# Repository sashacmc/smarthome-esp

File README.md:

# smarthome-esp
Eagle schemes for my esp8266 boards

## esp07_1w.*
Simple board to route 1-wire devices by esp07.
Fitted to standard phone socket.

## esp07_4PIO_6S_v2.*
My main smarthome esp07 board.
Provide:
* Four 220V outputs.
* Six dry contact (5V) inputs
* Two ext power (12V)
* Measure temperature and humidity by AM2302
* Measure illuminate by TSL2561

## esp07_co2.*
My first esp07 board
Provide:
* Measure temperature and pressure by BMP280
* Measuring CO2 level by MH-Z14

HAS BUGS WITH POWER CONSUMPTION FOR MH-Z14!!!

## esp07_ups.*
Board to control UPS by emulating power button pressing.
Has two power sources (from line and from UPS)

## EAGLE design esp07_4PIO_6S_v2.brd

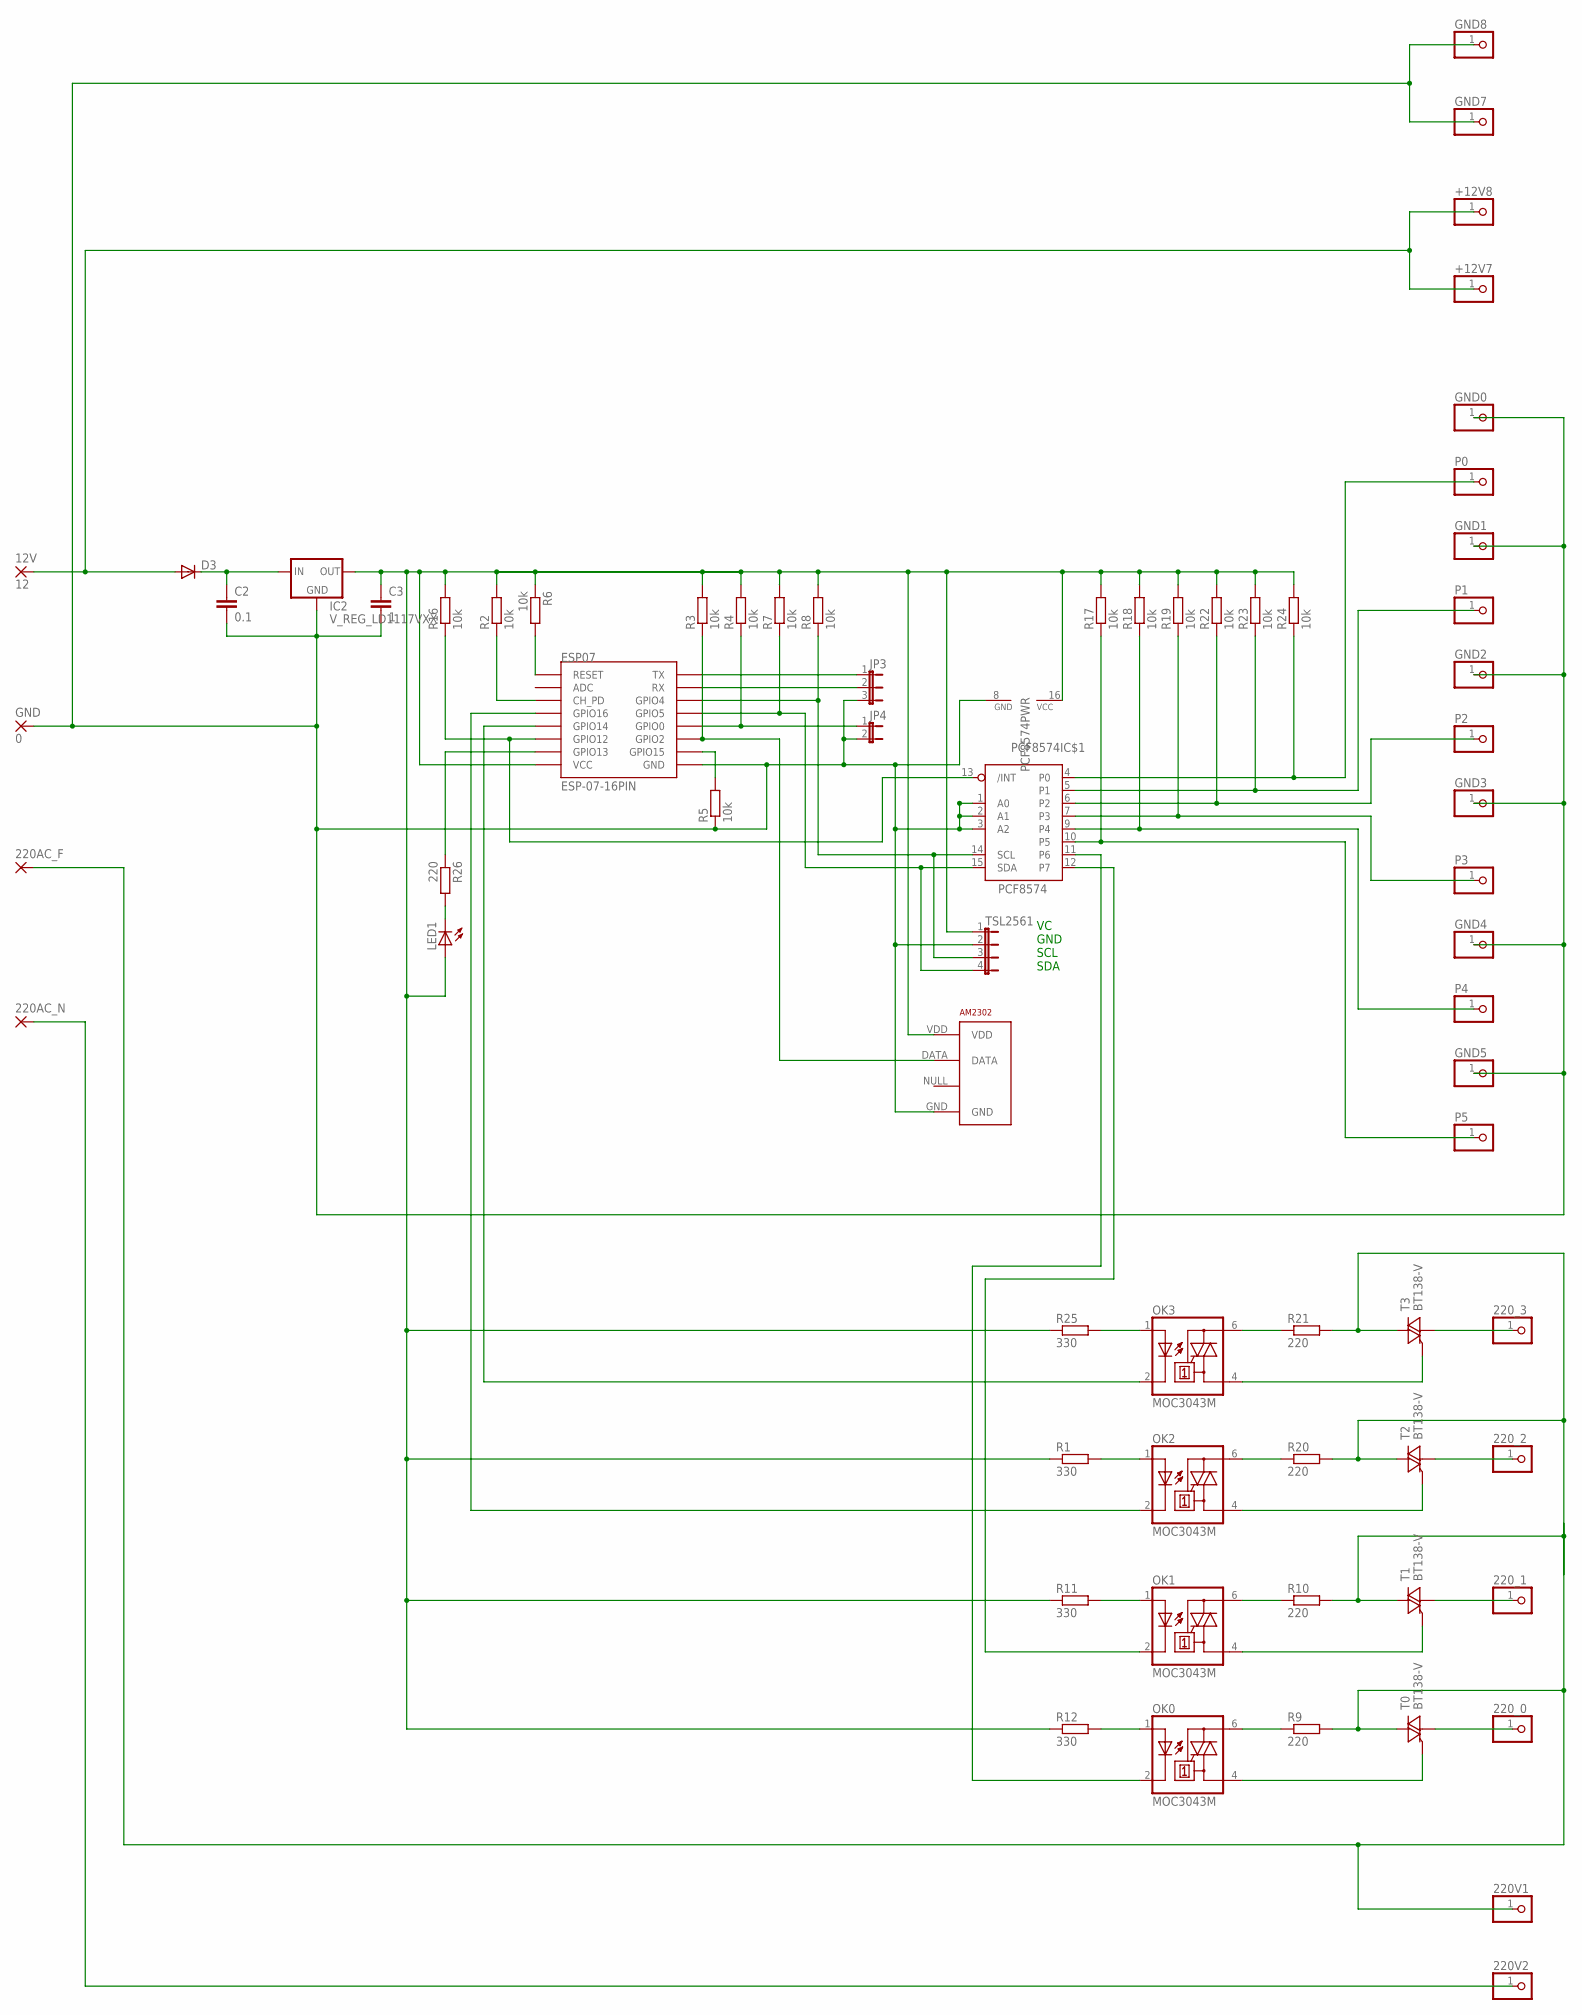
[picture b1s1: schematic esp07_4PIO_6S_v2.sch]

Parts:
12V: 12; 2,54/0,9
220AC_F, 220AC_N: 1,6/0,9
220V1, 220V2, 220_0, 220_1, 220_2, 220_3: PINHD-1X1; 1X01
+12V7, +12V8: PINHD-1X1; 1X01
AM2302: RHT03_DHT-22_AM2302WIRED; AM2302
C2: 0.1; C0805
C3: 1; C1206
D3: DIODE-SOD80C; SOD80C
ESP07: ESP-07-16PIN
GND: 0; 2,54/0,9
GND0, GND1, GND2, GND3, GND4, GND5, GND7, GND8: PINHD-1X1; 1X01
IC2: V_REG_LD1117VXX; 78XXL
JP3: JP2E; JP2
JP4: JP1E; JP1
LED1: LEDCHIPLED_1206; CHIPLED_1206
OK0, OK1, OK2, OK3: MOC3043M; DIL06
P0, P1, P2, P3, P4, P5: PINHD-1X1; 1X01
PCF8574: PCF8574; SOP16
R1, R11, R12, R25: 330; M1206
R2, R3, R4, R5, R6, R7, R8, R16, R17, R18, R19, R22, R23, R24: 10k; R1206
R9, R10, R20, R21, R26: 220; M1206
T0, T1, T2, T3: BT138-V; TO220BV
TSL2561: JP4E; JP4

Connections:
200V: 220AC_F.1, 220V1.1, R9.2, R10.2, R20.2, R21.2, T0.T2 (A2), T1.T2 (A2), T2.T2 (A2), T3.T2 (A2)
unnamed: 12V.1, +12V7.1, +12V8.1, D3.A
unnamed: OK3.1 (A), R25.2
unnamed: P0.1, PCF8574.4 (P0), R24.1
unnamed: ESP07.TX, JP3.1
unnamed: ESP07.RX, JP3.2
unnamed: P1.1, PCF8574.5 (P1), R23.1
unnamed: OK1.2 (C), PCF8574.12 (P7)
unnamed: P2.1, PCF8574.6 (P2), R22.1
unnamed: ESP07.GPIO13, R26.1
unnamed: ESP07.CH_PD, R2.1
unnamed: ESP07.REST (RESET), R6.2
unnamed: P3.1, PCF8574.7 (P3), R19.1
unnamed: OK0.2 (C), PCF8574.11 (P6)
unnamed: P4.1, PCF8574.9 (P4), R18.1
unnamed: P5.1, PCF8574.10 (P5), R17.1
unnamed: LED1.C, R26.2
unnamed: ESP07.GPIO14, OK3.2 (C)
unnamed: OK2.1 (A), R1.2
unnamed: OK1.1 (A), R11.2
unnamed: OK1.6 (A2), R10.1
unnamed: OK0.6 (A2), R9.1
unnamed: OK1.4 (A1), T1.G
unnamed: C2.1, D3.C, IC2.OUT (IN)
unnamed: OK0.4 (A1), T0.G
unnamed: 220_1.1, T1.T1 (A1)
unnamed: ESP07.GPIO4, PCF8574.14 (SCL), R8.1, TSL2561.3
unnamed: 220_2.1, T2.T1 (A1)
unnamed: 220_0.1, T0.T1 (A1)
unnamed: AM2302.VDD, C3.1, ESP07.VCC, IC2.GND (OUT), LED1.A, PCF8574.16 (VCC), R1.1, R2.2, R3.2, R4.2, R6.1, R7.2, R8.2, R11.1, R12.1, R16.2, R17.2, R18.2, R19.2, R22.2, R23.2, R24.2, R25.1, TSL2561.1
unnamed: OK0.1 (A), R12.2
unnamed: OK3.6 (A2), R21.1
unnamed: OK2.6 (A2), R20.1
unnamed: OK3.4 (A1), T3.G
unnamed: OK2.4 (A1), T2.G
unnamed: 220_3.1, T3.T1 (A1)
unnamed: ESP07.GPIO16, OK2.2 (C)
unnamed: 220AC_N.1, 220V2.1
unnamed: ESP07.GPIO5, PCF8574.15 (SDA), R7.1, TSL2561.4
unnamed: AM2302.GND, C2.2, C3.2, ESP07.GND, GND.1, GND0.1, GND1.1, GND2.1, GND3.1, GND4.1, GND5.1, GND7.1, GND8.1, IC2.IN (GND), JP3.3, JP4.2, PCF8574.1 (A0), PCF8574.2 (A1), PCF8574.3 (A2), PCF8574.8 (GND), R5.1, TSL2561.2
unnamed: ESP07.GPIO15, R5.2
unnamed: ESP07.GPIO0, JP4.1, R4.1
unnamed: AM2302.DATA, ESP07.GPIO2, R3.1
unnamed: ESP07.GPIO12, PCF8574.13 (/INT), R16.1

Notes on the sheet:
VC GND SCL SDA

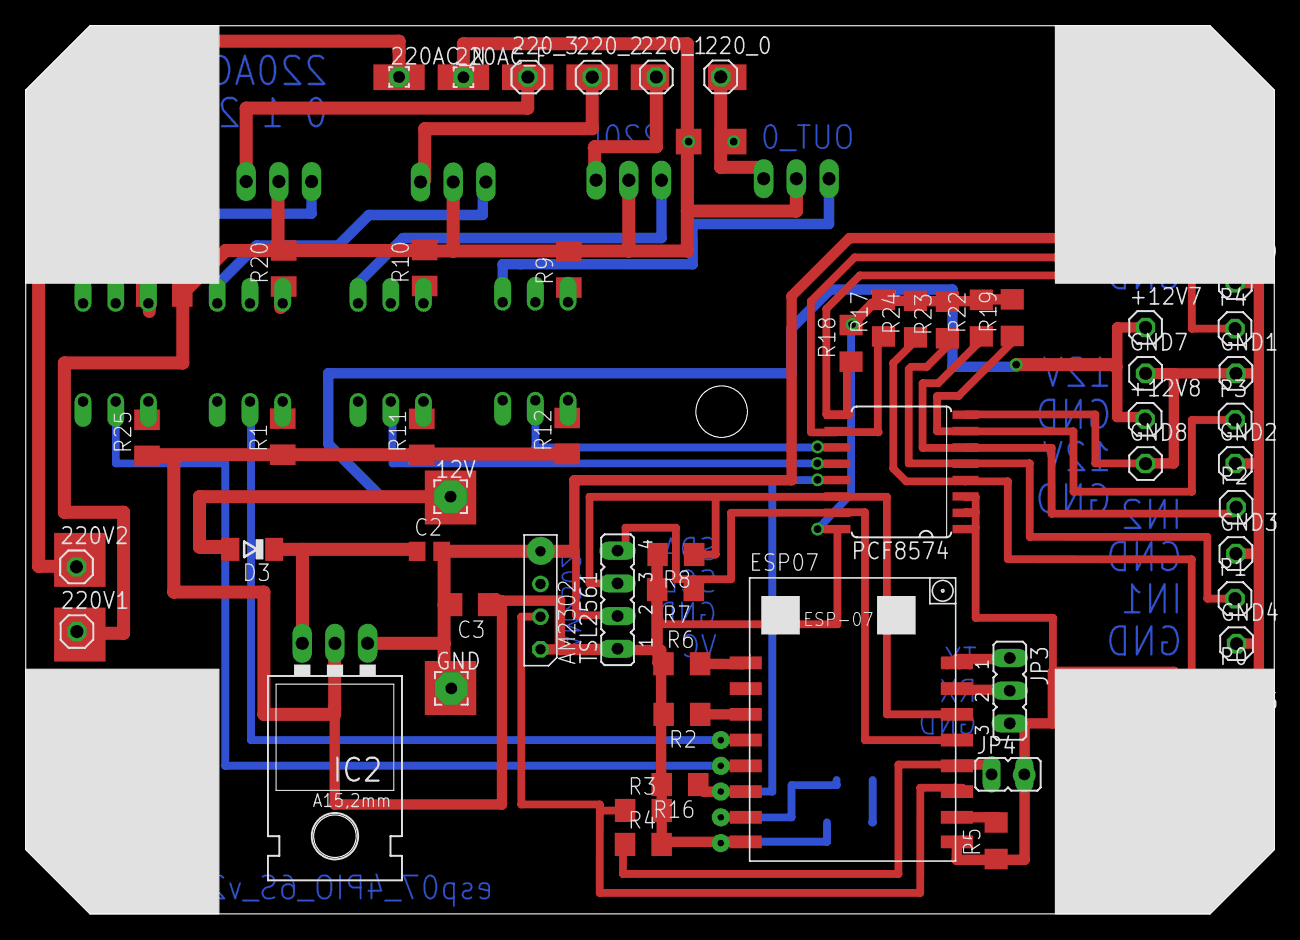
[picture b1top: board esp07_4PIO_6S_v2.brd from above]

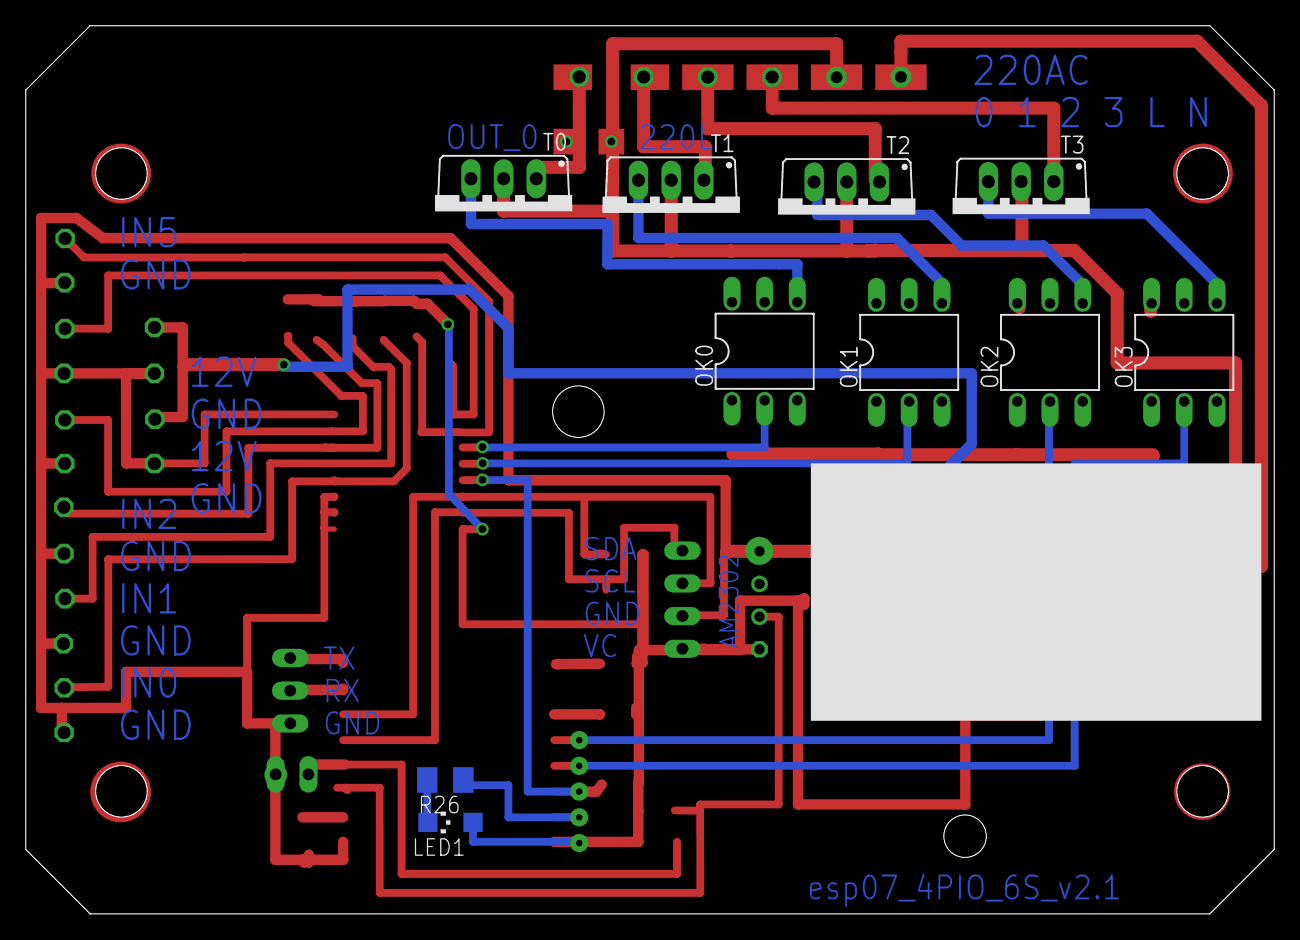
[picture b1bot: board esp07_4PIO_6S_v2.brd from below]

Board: 2 copper layers, 97.0 x 69.0 mm, 68 parts (10 on the bottom side), 44 nets.

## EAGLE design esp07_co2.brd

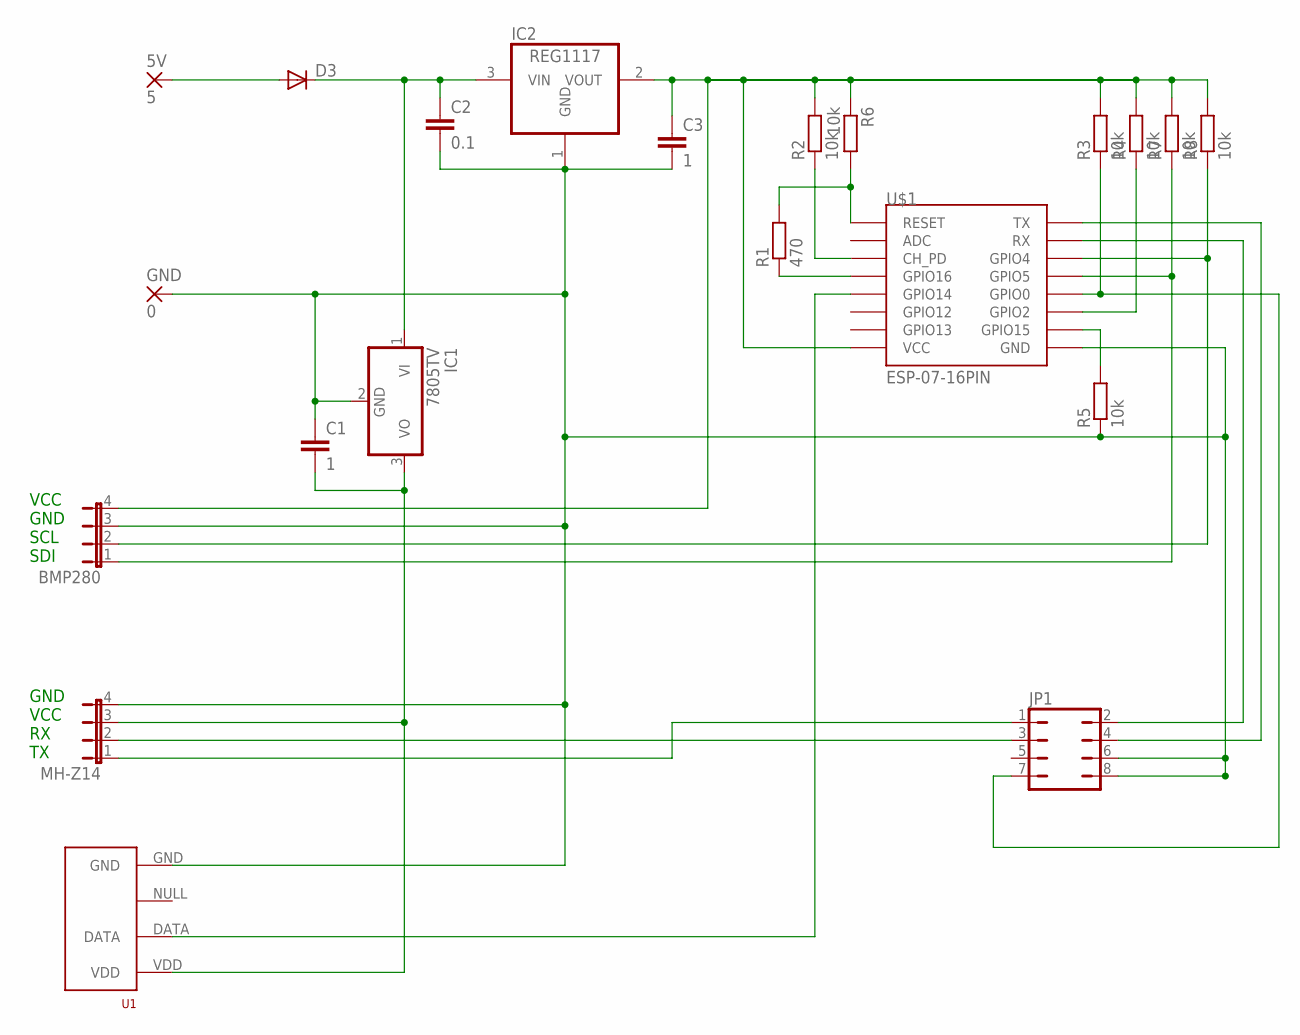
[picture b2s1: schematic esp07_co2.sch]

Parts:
5V: 5; 2,54/0,9
BMP280: JP4E; JP4
C1, C3: 1; C0805
C2: 0.1; C0805
D3: DIODE-SOD80C; SOD80C
GND: 0; 2,54/0,9
IC1: 7805TV; TO220V
IC2: REG1117; SOT223
JP1: JP4Q
MH-Z14: JP4E; JP4
R1: 470; R1206
R2, R3, R4, R5, R6, R7, R8: 10k; R1206
U1: RHT03_DHT-22_AM2302RA; RHT03_DHT-22/RA
U$1: ESP-07-16PIN

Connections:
unnamed: 5V.1, D3.A
unnamed: BMP280.2, R8.1, U$1.GPIO4
unnamed: BMP280.4, C3.1, IC2.2 (VOUT), R2.2, R3.2, R4.2, R6.1, R7.2, R8.2, U$1.VCC
unnamed: BMP280.3, C1.1, C2.2, C3.2, GND.1, IC1.2 (GND), IC2.1 (GND), JP1.6, JP1.8, MH-Z14.4, R5.1, U1.GND, U$1.GND
unnamed: JP1.4, U$1.TX
unnamed: JP1.2, U$1.RX
unnamed: R1.1, U$1.GPIO16
unnamed: R5.2, U$1.GPIO15
unnamed: JP1.7, R3.1, U$1.GPIO0
unnamed: R4.1, U$1.GPIO2
unnamed: R2.1, U$1.CH_PD
unnamed: R1.2, R6.2, U$1.REST (RESET)
unnamed: JP1.3, MH-Z14.2
unnamed: JP1.1, MH-Z14.1
unnamed: U1.DATA, U$1.GPIO14
unnamed: BMP280.1, R7.1, U$1.GPIO5
unnamed: C1.2, IC1.3 (VO), MH-Z14.3, U1.VDD
unnamed: C2.1, D3.C, IC1.1 (VI), IC2.3 (VIN)

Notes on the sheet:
VCC GND SCL SDI
GND VCC RX TX

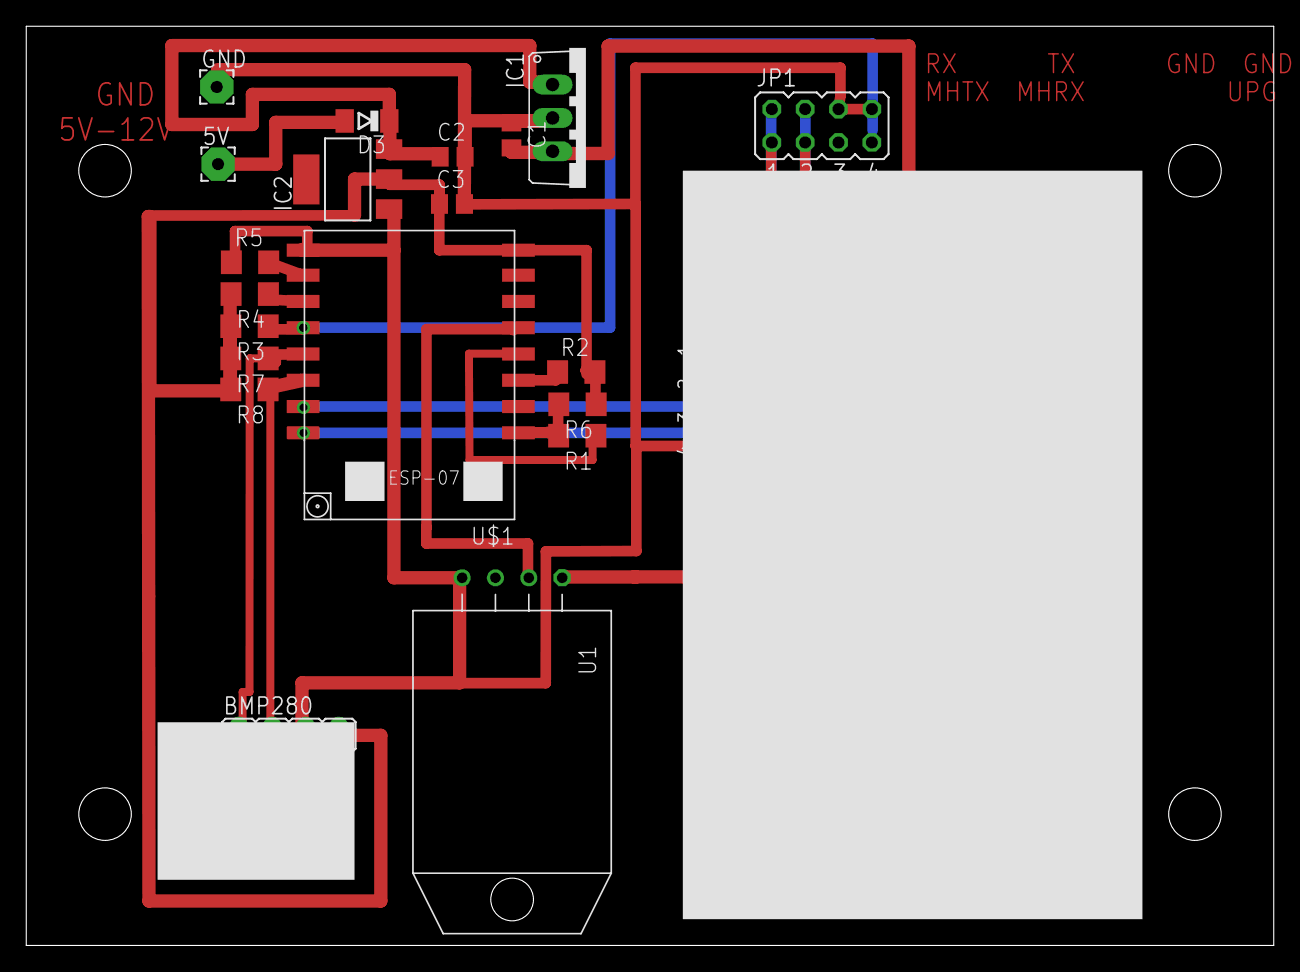
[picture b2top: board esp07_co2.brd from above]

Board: 2 copper layers, 95.0 x 70.0 mm, 21 parts (0 on the bottom side), 18 nets.

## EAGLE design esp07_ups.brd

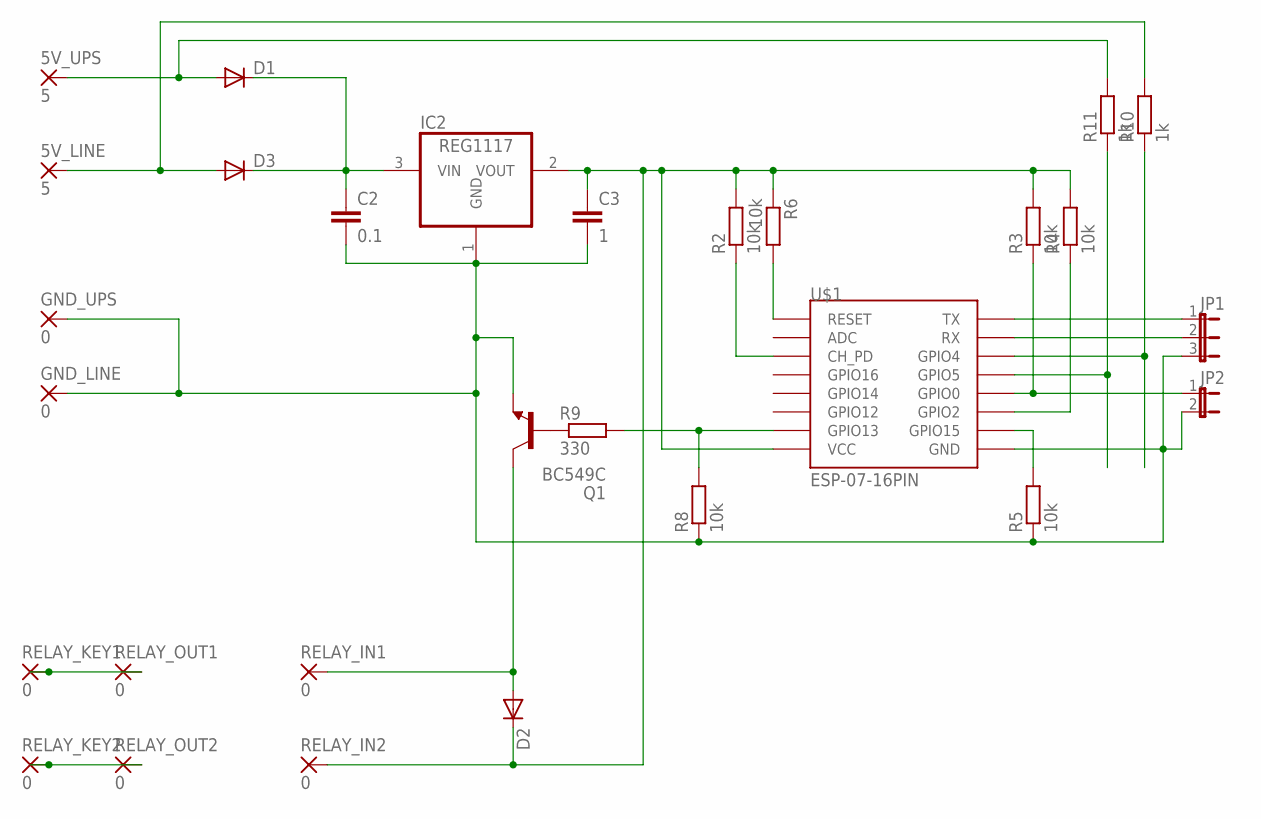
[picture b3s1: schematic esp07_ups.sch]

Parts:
5V_LINE, 5V_UPS: 5; 2,15/1,0
C2: 0.1; C0805
C3: 1; C0805
D1, D2, D3: DIODE-SOD80C; SOD80C
GND_LINE: 0; 2,15/1,0
GND_UPS: 0; 2,15/1,0
IC2: REG1117; SOT223
JP1: JP2E; JP2
JP2: JP1E; JP1
Q1: BC549C; TO92-EBC
R2, R3, R4, R5, R6, R8: 10k; R1206
R9: 330; R1206
R10, R11: 1k; R1206
RELAY_IN1, RELAY_IN2: 0; 3,17/1,1
RELAY_KEY1, RELAY_KEY2: 0; 2,15/1,0
RELAY_OUT1, RELAY_OUT2: 0; 3,17/1,1
U$1: ESP-07-16PIN

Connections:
unnamed: R8.2, R9.2, U$1.GPIO13
unnamed: Q1.B, R9.1
unnamed: C3.1, D2.C, IC2.2 (VOUT), R2.2, R3.2, R4.2, R6.1, RELAY_IN2.1, U$1.VCC
unnamed: C2.2, C3.2, GND_LINE.1, GND_UPS.1, IC2.1 (GND), JP1.3, JP2.2, Q1.E, R5.1, R8.1, U$1.GND
unnamed: JP1.1, U$1.TX
unnamed: JP1.2, U$1.RX
unnamed: 5V_UPS.1, D1.A, R11.2
unnamed: R5.2, U$1.GPIO15
unnamed: JP2.1, R3.1, U$1.GPIO0
unnamed: R4.1, U$1.GPIO2
unnamed: R2.1, U$1.CH_PD
unnamed: R6.2, U$1.REST (RESET)
unnamed: R11.1, U$1.GPIO5
unnamed: 5V_LINE.1, D3.A, R10.2
unnamed: D2.A, Q1.C, RELAY_IN1.1
unnamed: R10.1, U$1.GPIO4
unnamed: RELAY_KEY1.1, RELAY_OUT1.1
unnamed: RELAY_KEY2.1, RELAY_OUT2.1
unnamed: C2.1, D1.C, D3.C, IC2.3 (VIN)

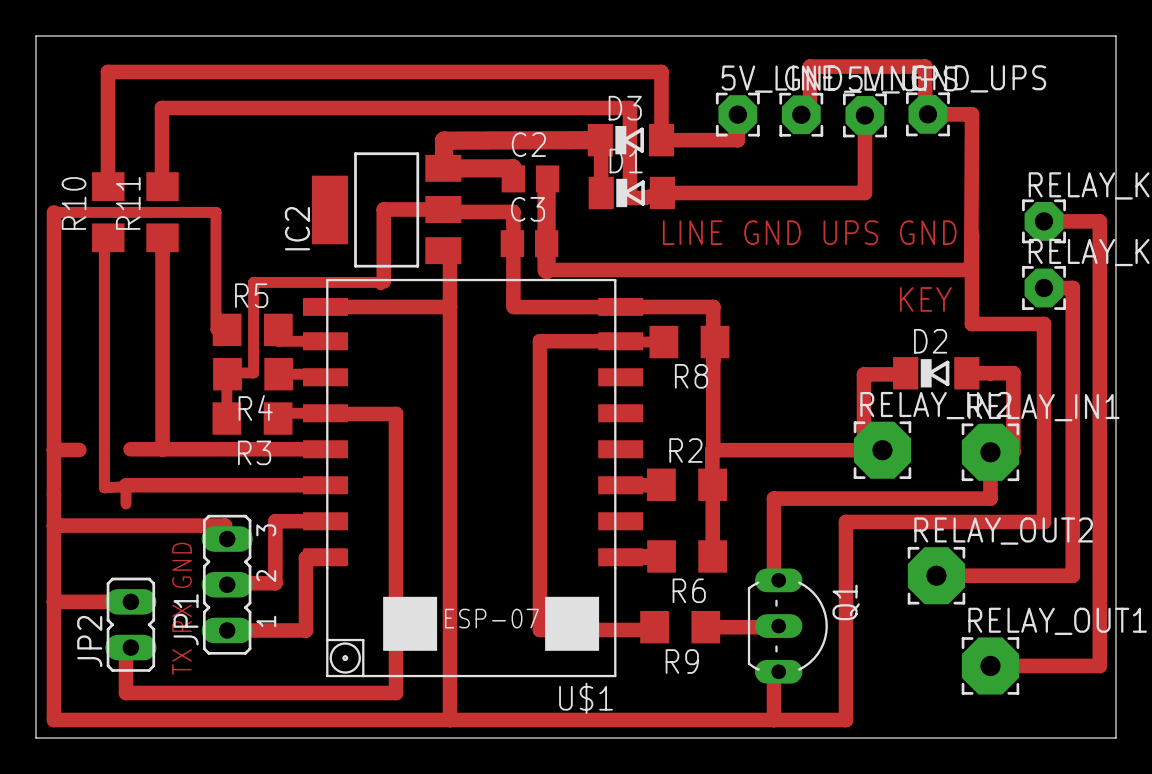
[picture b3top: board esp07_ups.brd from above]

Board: 2 copper layers, 60.0 x 39.0 mm, 29 parts (0 on the bottom side), 19 nets.

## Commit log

2017-05-16 Initial release.
2019-09-07 Small design update and enhancement for PCB order

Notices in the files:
parts and their libraries:
SparkFun: Licensing: CC v3.0 Share-Alike You are welcome to use this library for commercial purposes.
